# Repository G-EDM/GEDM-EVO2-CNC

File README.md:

# Schematics, Gerber files and Kicad projects for the PCBs
[>>> Schematics, Gerber files, Kicad projects and PCBway links <<<](https://github.com/G-EDM/GEDM-EVO2-CNC/tree/main/files/schematics-and-gerbers)
</br>
</br>

# GEDM-EVO2-CNC
Gantry based 3 axis CNC router with heavy duty 3d printed parts

```diff
  ______         ________ _______  __       __      ________ __     __  ______       ______ ______ 
 /      \       |        \       \|  \     /  \    |        \  \   |  \/      \     |      \      \
|  ▓▓▓▓▓▓\      | ▓▓▓▓▓▓▓▓ ▓▓▓▓▓▓▓\ ▓▓\   /  ▓▓    | ▓▓▓▓▓▓▓▓ ▓▓   | ▓▓  ▓▓▓▓▓▓\     \▓▓▓▓▓▓\▓▓▓▓▓▓
| ▓▓ __\▓▓______| ▓▓__   | ▓▓  | ▓▓ ▓▓▓\ /  ▓▓▓    | ▓▓__   | ▓▓   | ▓▓ ▓▓  | ▓▓      | ▓▓   | ▓▓  
| ▓▓|    \      \ ▓▓  \  | ▓▓  | ▓▓ ▓▓▓▓\  ▓▓▓▓    | ▓▓  \   \▓▓\ /  ▓▓ ▓▓  | ▓▓      | ▓▓   | ▓▓  
| ▓▓ \▓▓▓▓\▓▓▓▓▓▓ ▓▓▓▓▓  | ▓▓  | ▓▓ ▓▓\▓▓ ▓▓ ▓▓    | ▓▓▓▓▓    \▓▓\  ▓▓| ▓▓  | ▓▓      | ▓▓   | ▓▓  
| ▓▓__| ▓▓      | ▓▓_____| ▓▓__/ ▓▓ ▓▓ \▓▓▓| ▓▓    | ▓▓_____   \▓▓ ▓▓ | ▓▓__/ ▓▓     _| ▓▓_ _| ▓▓_ 
 \▓▓    ▓▓      | ▓▓     \ ▓▓    ▓▓ ▓▓  \▓ | ▓▓    | ▓▓     \   \▓▓▓   \▓▓    ▓▓    |   ▓▓ \   ▓▓ \
  \▓▓▓▓▓▓        \▓▓▓▓▓▓▓▓\▓▓▓▓▓▓▓ \▓▓      \▓▓     \▓▓▓▓▓▓▓▓    \▓     \▓▓▓▓▓▓      \▓▓▓▓▓▓\▓▓▓▓▓▓
```

# Downloadlinks for the freecad files
    The router file is a little crappy. The extrusions/tank/rails of the frame are not a the correct position and the Y ballscrew is too short etc.
    But it can be used

[>>> G-EDM EVOII Wire extension FreeCAD Project <<<](https://drive.google.com/file/d/1ZBrTBwRvTHIMtCySQIoWtpVMdJbfWR3E/view)
</br>
[>>> G-EDM EVOII Router FreeCAD Project <<<](https://drive.google.com/file/d/1OkYVYsVrToy4-q0G6XMzgWKsSyYXRRj4/view)
</br>
</br>

# Responsible for the content provided
    Lautensack Roland (Germany)
    Contact: goblin-dev@proton.me

# This project is still a work in progress and not fully finished yet

The GEDM-EVO2 Gantry Router uses heavy duty 3D printed parts, strong HGR20 linear rails, ballscrews and heavy profiles (40x160).

With only a few upgrades/changes it will be able to not only do EDM but also mill wood and smaller aluminum parts.

In order to do those milling jobs it may require a second ballscrew on the left side.

The wire extension used in the images is the one designed by Alex Treseder for the PicoEDM:
https://github.com/alextreseder/picoEDM

Not fully finished. Z axis is still missing and the massive aluminum plate on the front is temporary.

Check out the youtube channel:

# Legal notes

    The author of this project is in no way responsible for whatever people do with it.

    No warranty. 

# License

    All files provided are for private use only if not declared otherwise and any form of commercial use or redistribution of the protected files is prohibited. 

# Follow the project:

[>>> Follow the project on Youtube <<<](https://www.youtube.com/@G-EDM/videos)

[>>> Stay informed on Hackaday <<<](https://hackaday.io/project/190371-g-edm)

[>>> Get involved on Discord <<<](https://discord.gg/9cTsyDkEbe)

# Donations

    * Developement is not always as fast as it could be if you're poor. You want to donate something? 
    * Paypal: paypal.me/gedmdev
    * Bitcoin: bc1qkz8vwrd3pupewdtyg09qj9nv249vlgdy4ffhyv

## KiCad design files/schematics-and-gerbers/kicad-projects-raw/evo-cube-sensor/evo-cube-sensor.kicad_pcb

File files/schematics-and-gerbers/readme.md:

# Update

Added the new EVOIII PCB. This board was designed for easier manufacturing and is a replacement for the sensorboard and the pulseboard. It has both integrated on a single PCB.

The PCBs can be ordered on PCBway using following links:

# Motionboard
https://www.pcbway.com/project/shareproject/G_EDM_Low_budget_DIY_Wire_EDM_machine_34e1e043.html

# EVOIII Board (Sensorboard and Pulseboard on one PCB)
https://www.pcbway.com/project/shareproject/G_EDM_EVOIII_board_Low_budget_DIY_Wire_EDM_machine_482d5b7a.html

<br/><br/><br/><br/>
# If the EVOIII board is used the following two PCBs are not needed.
<br/><br/>

# Sensorboard (Not needed if the EVOIII board is used)
https://www.pcbway.com/project/shareproject/G_EDM_Low_budget_DIY_Wire_EDM_machine_sensorboard_24b74366.html

# Pulseboard (Not needed if the EVOIII board is used)
https://www.pcbway.com/project/shareproject/G_EDM_Low_budget_DIY_Wire_EDM_machine_pulseboard_8975f488.html

The full electronic enclosure contains the control panel with the ESP32 motion controller and a touch screen and the spark generator.

The pulseboard and the sensing unit are two dedicated PCBs stacked on top of eachother.

The sensing unit is not bound to the G-EDM pulseboard and can be used with a custom generator as well.

Currently only the schmeatics of the pulseboard PCB is uploaded here.

Sennsing unit / motionboard and gerber files will follow.

The pulseboard can be used as stand-alone board too but the sensing is not comparable to the new sense circuit that is able to capture raw watercontact and even the tiniest discharges.

Files currently provided:

Schematics:
```diff
+ Pulseboard EVO² - yes
```
```diff
+ Sensing Unit EVO² - yes
```
```diff
+ Motionboard EVO² - yes
```

Gerber files:
```diff
+ Pulseboard EVO² - yes
```
```diff
+ Sensing Unit EVO² - yes
```
```diff
+ Motionboard EVO² - yes
```

BOM:
```diff
+ Pulseboard EVO² - yes
```
```diff
+ Sensing Unit EVO² - yes
```
```diff
+ Motionboard EVO² - yes
```

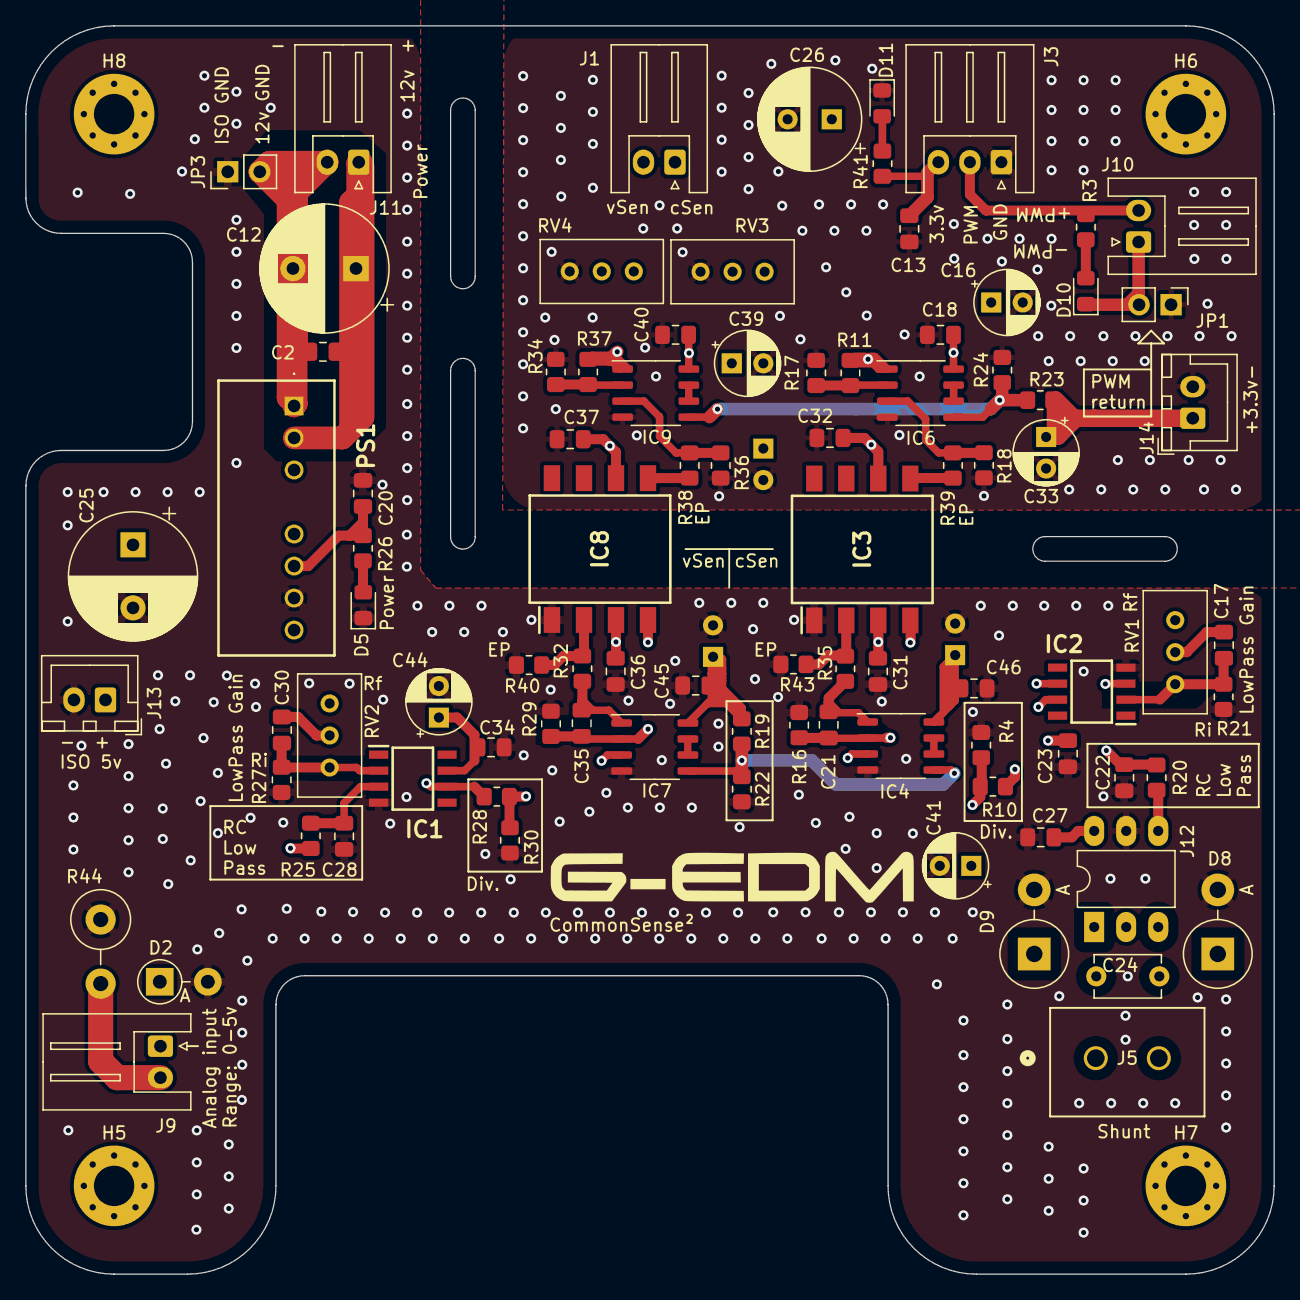
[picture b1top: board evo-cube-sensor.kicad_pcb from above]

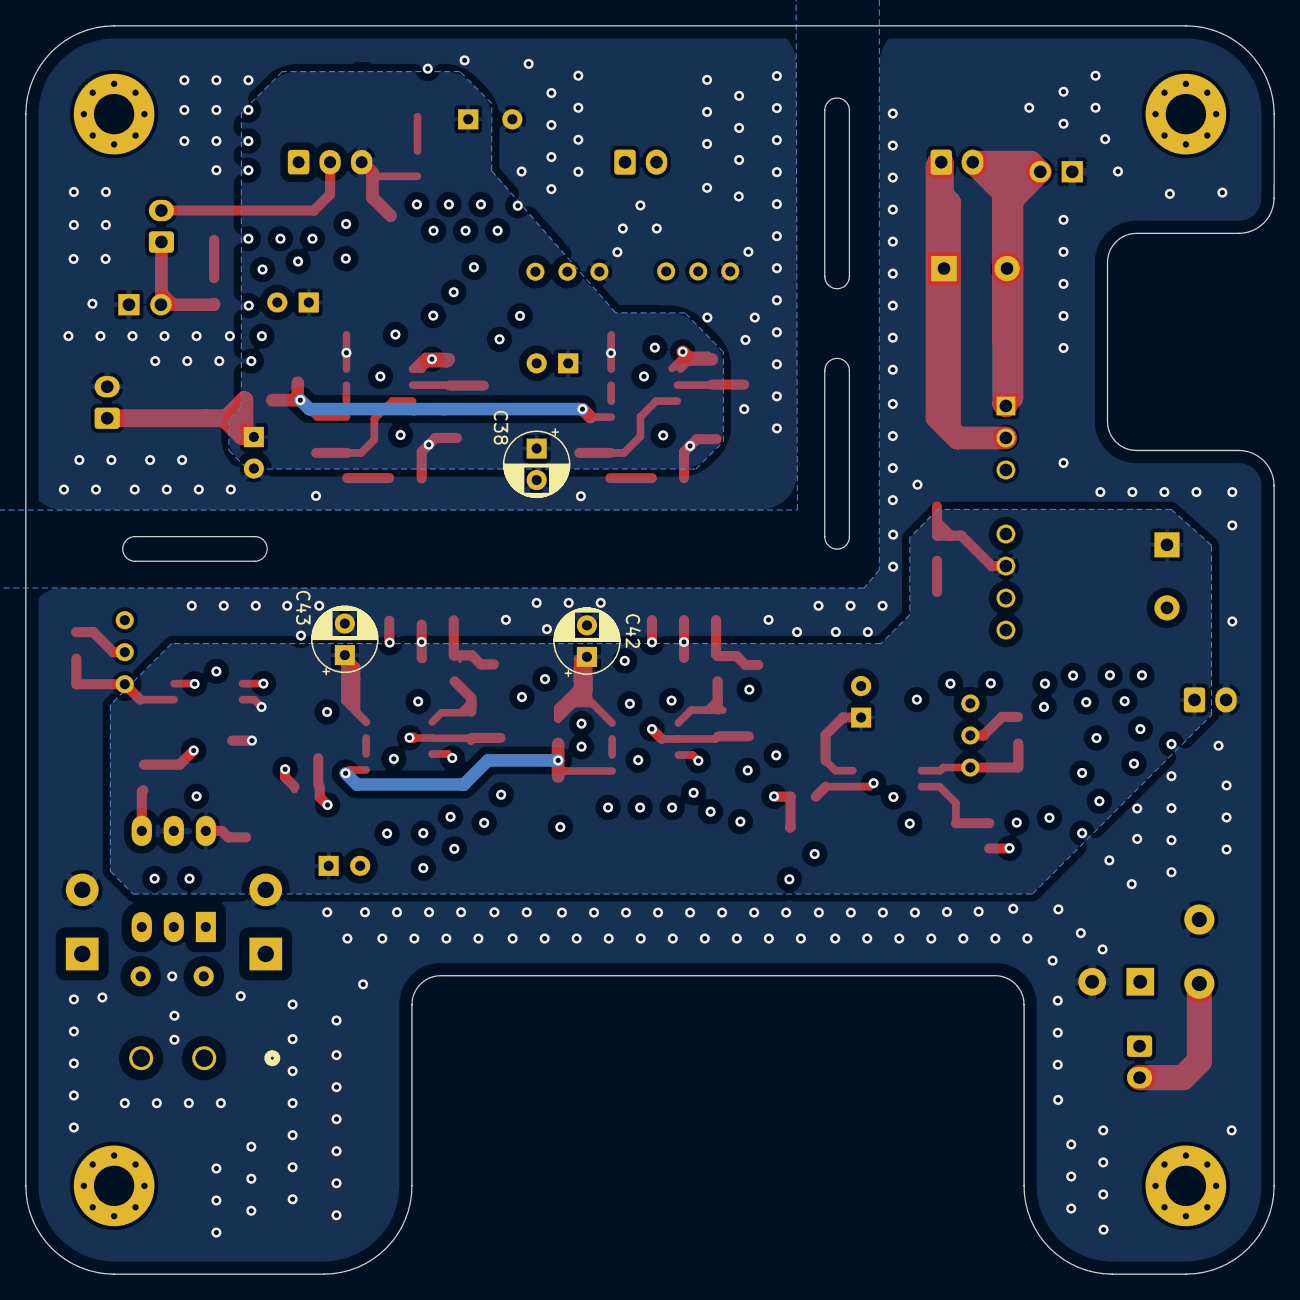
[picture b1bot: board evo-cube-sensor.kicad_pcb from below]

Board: 4 copper layers, 99.0 x 99.0 mm, 96 parts (3 on the bottom side), 46 nets.

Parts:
C2, C13, C18, C20, C23, C27, C31, C32, C34, C36, C37, C40, C45, C46: 0.1uf-50v-x7r 08055C104K4T2A; C_0805_2012Metric_Pad1.18x1.45mm_HandSolder
C12, C25: 220uf50v RD1H227M1012M128; CP_Radial_D10.0mm_P5.00mm
C16, C39, C41, C44: 47uf63v RD1J476M6L011M18; CP_Radial_D5.0mm_P2.50mm
C17, C30: 47pf X; C_0805_2012Metric_Pad1.18x1.45mm_HandSolder
C21, C22, C28, C35: 100pf50v X7R C0805C101J5RACTU; C_0805_2012Metric_Pad1.18x1.45mm_HandSolder
C24: C100pf500v KERKO-500 100P; C_Disc_D5.1mm_W3.2mm_P5.00mm
C26: 220uf35v RD1V227M0811M160; CP_Radial_D8.0mm_P3.50mm
C33, C38, C42, C43: X; CP_Radial_D5.0mm_P2.50mm
D2: 5.1v Zener (Not used); D_DO-41_SOD81_P3.81mm_Vertical_AnodeUp
D5, D11: SM0805UGC; LED_0805_2012Metric_Pad1.15x1.40mm_HandSolder
D8, D9: 1N5379B 110v Zener; D_DO-201_P5.08mm_Vertical_AnodeUp
D10: APT2012LVBC/D; LED_0805_2012Metric_Pad1.15x1.40mm_HandSolder
H5: MountingHole_Pad; MountingHole_3.2mm_M3_Pad_Via
H6, H7, H8: MountingHole; MountingHole_3.2mm_M3_Pad_Via
IC1, IC2: OPA350UA; SOIC127P600X175-8N
IC3, IC8: HCNR201-500E; SOP254P1230X400-8N
IC4, IC7: LM358F-GE2; SOP-8_3.9x4.9mm_P1.27mm
IC6, IC9: OPA2350UA; SOP-8_3.9x4.9mm_P1.27mm
J1, J9, J10, J11: JST_XH_S2B-XH-A_1x02_P2.50mm_Horizontal
J3: JST_XH_S3B-XH-A_1x03_P2.50mm_Horizontal
J5: 1776138-2 and 796641-2; CONN2_796643-2_TEC
J12: INA293B3QDBVRQ1 on PCB3007-1 Adapter; DIP-6_W7.62mm_LongPads
J13, J14: JST XHP-2; JST_XH_B2B-XH-A_1x02_P2.50mm_Vertical
JP1: Jumper_2_Bridged; PinHeader_1x02_P2.54mm_Vertical
JP3: 1x02 pin header jumper cap (149-3-002-F0-XS); PinHeader_1x02_P2.54mm_Vertical
PS1: RS3K-2405SZ/H3; RS3K2405SZH3
R3: 220; R_0805_2012Metric_Pad1.20x1.40mm_HandSolder
R4, R30: 4k7; R_0805_2012Metric_Pad1.20x1.40mm_HandSolder
R10, R19, R22, R23, R24, R28: 10k 1% WRIS-RSKS 560112120004; R_0805_2012Metric_Pad1.20x1.40mm_HandSolder
R11, R17, R34, R37: 20k RK73H2ARTTD2002F; R_0805_2012Metric_Pad1.20x1.40mm_HandSolder
R16, R18, R29, R36: 100k 1% Würth WRIS-RSKS 560112120013; R_0805_2012Metric_Pad1.20x1.40mm_HandSolder
R20, R21, R25, R27: 1kOhm 5% ERJ-T06J102V; R_0805_2012Metric_Pad1.20x1.40mm_HandSolder
R26: 560Ohm RK73B2ATTD561J; R_0805_2012Metric_Pad1.20x1.40mm_HandSolder
R32, R35: 200Ohm WRIS-RSKS 560112120015; R_0805_2012Metric_Pad1.20x1.40mm_HandSolder
R38, R39: Zero Ohm RCC08050000Z0EA; R_0805_2012Metric_Pad1.20x1.40mm_HandSolder
R40, R43: 10k?; R_0805_2012Metric_Pad1.20x1.40mm_HandSolder
R41: 220 Ohm 5% ERJ-T06J221V; R_0805_2012Metric_Pad1.20x1.40mm_HandSolder
R44: 1kOhm; R_Axial_DIN0414_L11.9mm_D4.5mm_P5.08mm_Vertical
RV1, RV2, RV3, RV4: 3296W Poti 10kOhm; Potentiometer_Bourns_3296W_Vertical

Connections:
1,65V: IC6.5 (2IN+), IC9.5 (2IN+), R23.2, R24.1
2.5V: IC4.5 (2IN+), IC7.5 (2IN+), R19.2, R22.1
+12v-from-pb: C2.1, C12.1, J11.1, PS1.2 (+VIN)
ESP3.3v: C13.1, C16.1, C18.1, C26.1, C32.1, C33.1, C37.1, C38.1, C39.1, C40.1, IC3.6 (PD2_CATHODE), IC6.8 (VCC), IC8.6 (PD2_CATHODE), IC9.8 (VCC), J3.3, J14.1, R23.1, R41.2
GND1: C13.2, C16.2, C18.2, C26.2, C32.2, C33.2, C37.2, C38.2, C39.2, C40.2, D11.1 (K), IC6.4 (GND), IC9.4 (GND), J3.1, J14.2, JP1.1 (A), R17.1, R18.1, R24.2, R34.1, R36.1, RV3.3, RV4.3
GND3: C20.2, C22.2, C23.2, C25.2, C27.1, C28.2, C31.1, C34.2, C36.1, C41.2, C42.2, C43.2, C44.2, C45.1, C46.1, D2.2 (A), D5.1 (K), D8.2 (A), D9.2 (A), IC1.4 (V-), IC2.4 (V-), IC3.1 (LED_CATHODE), IC4.4 (GND), IC7.4 (GND), IC8.1 (LED_CATHODE), J12.5, J13.2, JP3.1 (A), PS1.7 (-VOUT), R4.2, R16.1, R21.2, R22.2, R27.2, R29.1, R30.2, R40.2, R43.2, R44.1
ISO+5v: C20.1, C23.1, C25.1, C27.2, C31.2, C34.1, C36.2, C41.1, C42.1, C43.1, C44.1, C45.2, C46.2, IC1.7 (V+), IC2.7 (V+), IC3.3 (PD1_CATHODE), IC4.8 (VCC), IC7.8 (VCC), IC8.3 (PD1_CATHODE), J12.6, J13.1, PS1.6 (+VOUT), R19.1, R26.2
Isolated-csense-out: J1.1, RV3.2
Isolated-vsense-out: J1.2, RV4.2
unnamed: D2.1 (K), J9.1, R25.1
unnamed: D5.2 (A), R26.1
unnamed: C24.1, D8.1 (K), J5.2, J12.3
unnamed: C24.2, D9.1 (K), J5.1, J12.1
unnamed: D10.2 (A), R3.1
unnamed: D10.1 (K), J10.1, JP1.2 (B)
unnamed: D11.2 (A), R41.1
unnamed: C28.1, IC1.3 (+IN), R25.2
unnamed: C30.2, IC1.2 (-IN), R27.1, RV2.1
unnamed: C30.1, IC1.6 (OUTPUT), R28.2, RV2.2
unnamed: C22.1, IC2.3 (+IN), R20.2
unnamed: C17.2, IC2.2 (-IN), R21.1, RV1.1
unnamed: C17.1, IC2.6 (OUTPUT), R10.2, RV1.2
unnamed: IC3.2 (LED_ANODE), R35.1, R43.1
unnamed: C21.1, IC3.4 (PD1_ANODE), IC4.2 (1IN-), R16.2
unnamed: IC3.5 (PD2_ANODE), R39.1
unnamed: IC4.3 (1IN+), R4.1, R10.1
unnamed: C21.2, IC4.1 (1OUT), R35.2
unnamed: IC4.6 (2IN-), IC4.7 (2OUT)
unnamed: IC6.3 (1IN+), R18.2, R39.2
unnamed: IC6.2 (1IN-), R11.1, R17.2
unnamed: IC6.1 (1OUT), R11.2, RV3.1
unnamed: IC6.6 (2IN-), IC6.7 (2OUT)
unnamed: IC7.3 (1IN+), R28.1, R30.1
unnamed: C35.1, IC7.2 (1IN-), IC8.4 (PD1_ANODE), R29.2
unnamed: C35.2, IC7.1 (1OUT), R32.2
unnamed: IC7.6 (2IN-), IC7.7 (2OUT)
unnamed: IC8.2 (LED_ANODE), R32.1, R40.1
unnamed: IC8.5 (PD2_ANODE), R38.1
unnamed: IC9.3 (1IN+), R36.2, R38.2
unnamed: IC9.2 (1IN-), R34.2, R37.1
unnamed: IC9.1 (1OUT), R37.2, RV4.1
unnamed: IC9.6 (2IN-), IC9.7 (2OUT)
unnamed: J9.2, R44.2
unnamed: J12.4, R20.1
pwm-from-esp: J3.2, J10.2, R3.2
to-gnd2-on-pb: C2.2, C12.2, J11.2, JP3.2 (B), PS1.1 (-VIN)

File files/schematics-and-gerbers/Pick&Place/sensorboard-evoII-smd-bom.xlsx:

| G-EDM Sensorboard EVOII – SMD/SMT BOM
Item # | *Designator | *Qty | Manufacturer | *Mfg Part # | Description / Value | *Package/Footprint | Type | Your Instructions / Notes
1 | C2,C13,C18,C20,C23,C27,C31,C32,C34,C36,C37,C40,C45,C46 | 14 | KYOCERA AVX | 08055C104K4T2A | 0.1uf 50v X7R 10% MLCC | 0805 | SMD
2 | C21,C22,C28,C35 | 4 | KEMET | C0805C101J5RACTU | 100pF 50v X7R 5% MLCC | 0805 | SMD
3 | R38,R39 | 2 | Vishay / Dale | RCC08050000Z0EA | Zero Ohm 1/4W resistor jumper | 0805 | SMD
4 | R32,R35 | 2 | Würth | 560112120015 | 200 Ohm 1/4W 1% resistor | 0805 | SMD
5 | R3,R41 | 2 | Panasonic | ERJ-T06J221V | 220 Ohm 1/4W 5% resistor | 0805 | SMD
6 | R26 | 1 | KOA Speer | RK73B2ATTD561J | 560 Ohm 1/4W 5% resistor | 0805 | SMD
7 | R20,R21,R25,R27 | 4 | Panasonic | ERJ-T06J102V | 1 kOhm 1/4W 5% resistor | 0805 | SMD
8 | R4,R30 | 2 | Vishay / Dale | RCC08054K70FKEA | 4.7 kOhm 1/4W 1% resistor | 0805 | SMD
9 | R10,R19,R22,R23,R24,R28 | 6 | Würth | 560112120004 | 10 kOhm 1/4W 1% resistor | 0805 | SMD
10 | R11,R17,R34,R37 | 4 | KOA Speer | RK73H2ARTTD2002F | 20 kOhm 1/4W 1% resistor | 0805 | SMD
11 | R16,R18,R29,R36 | 4 | Würth | 560112120013 | 100 kOhm 1/4W 1% resistor | 0805 | SMD
12 | IC1,IC2 | 2 | Texas Instruments | OPA350UA | High Speed rail-to-rail OpAmp single channel | SOIC-8 | SMD | Please validate the footprint
13 | IC6,IC9 | 2 | Texas Instruments | OPA2350UA | High Speed rail-to-rail OpAmp dual channel | SOIC-8 | SMD | Please validate the footprint
14 | IC8,IC3 | 2 | Broadcom / Avago | HCNR201-500E | High Linear Optocoupler | SOP-8 | SMD | Please validate the footprint
15 | IC4,IC7 | 2 | ROHM Semiconductor | LM358F-GE2 | Dual Grnd Sense Op Amp | SOP-8 | SMD | Please validate the footprint
16 | D5,D11 | 2 | Bivar | SM0805UGC | LED green 20mA 2v | 0805 | SMD
17 | D10 | 1 | Kingbright | APT2012LVBC/D | LED blue low current (starts to emit at 2mA) 2,65v | 0805 | SMD

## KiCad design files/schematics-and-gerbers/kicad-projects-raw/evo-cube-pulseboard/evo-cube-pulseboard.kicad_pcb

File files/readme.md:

The sensorboard and the pulseboard are connected with 3 JST connectors.

The connectors are placed at the exact same position. Don't use the wrong connector!
I shared a few images in the past where the PWM from the sensorboard was connected to the 5v output on the
pulseboard. It will burn the ESP32.

Sensorboard => Pulseboard

J10 => J8
J11 => J2
J9  => J7

Before connecting J9 to J7 make sure the voltage on J7 is below 5v! This is important. Use the Poti on the pulseboard to adjust it while
the PSU is ON. The output of J7 should remain a little below 5v at the max voltage provided from the DPM.

If a higher voltage is used adjust the Poti again. 
If 80v is used the output should be 4.8v while the big terminal is at 80v.
If 60v is used the output should be 4.8v while the big terminal is at 60v.

The board has 100v Zener diodes. Up to 90v should be ok.

The sensorboard provides 3.3v output and isolated 5v output. It is not used for anything yet.
The pulseboard provides 5v output that is also not used.

The pulseboard also provides a 12v output to connect a fan but it is not tested. Cheap high speed fans may introduce noise. There are flyback diodes
but if used connect a larger slow fan like a 120mm arctic fan.

# DPM to pulseboard

Connect the DPM8605 negative to the left side of the left big terminal (J19) and the positive to the right side of the same terminal.

The left side of the right terminal (J17) is bridged to the left terminals positive. The Shunt and wire is always hot and only GND is switched.
Connect the left side of J17 to one side of the shunt and the other side is the spark positive output.
The spark negative goes back into the right side of J17.

# Shunt to sensorboard
Connect both sides of the shunt to the sensorboard J5. It is no problem to wire it wrong here. If connected wrong it will not provide a feedback but will not destroy anything. Just swap the wire if there is no feedback.

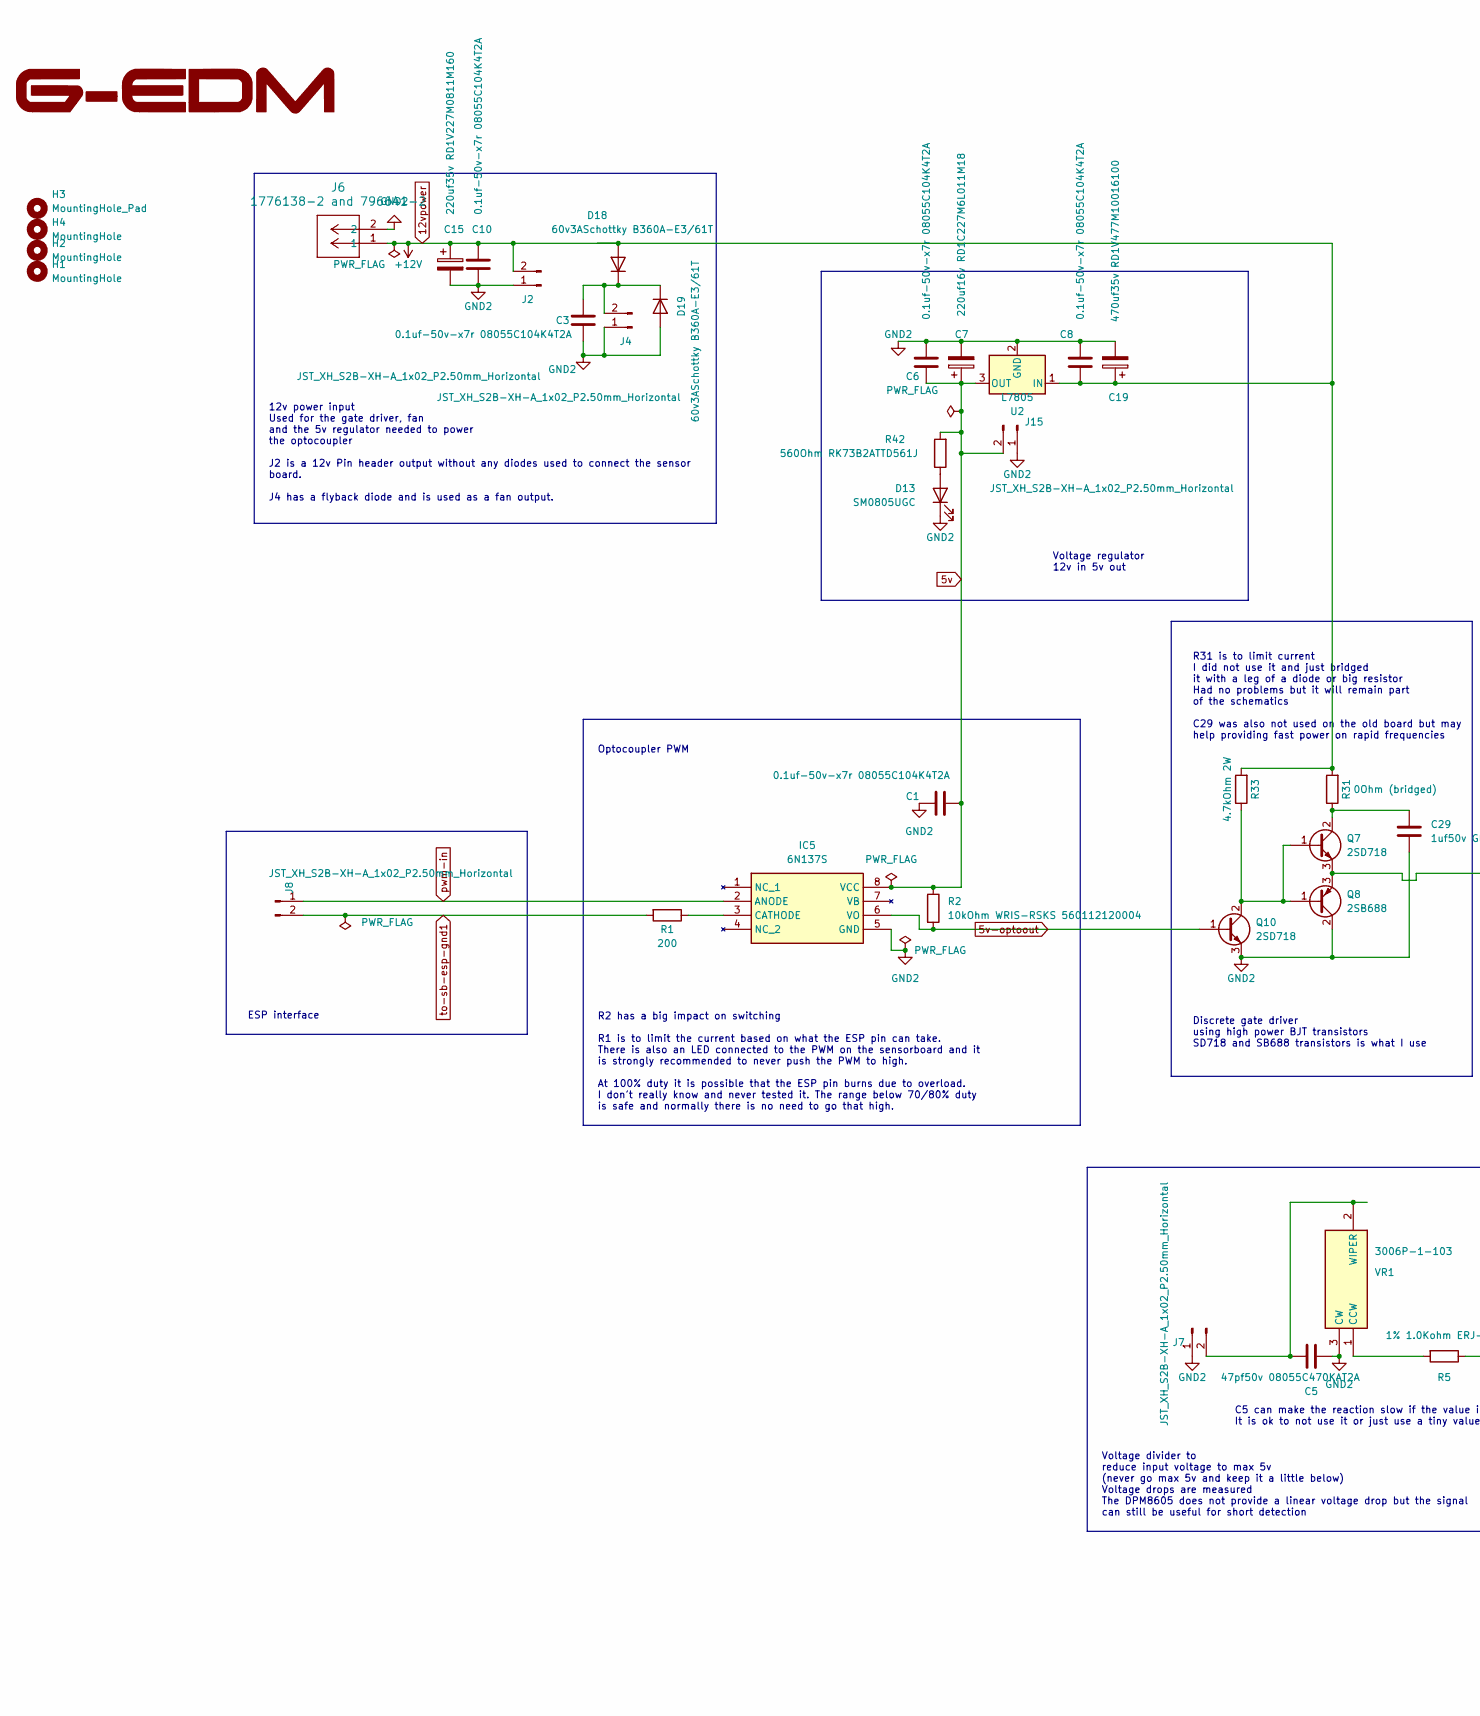
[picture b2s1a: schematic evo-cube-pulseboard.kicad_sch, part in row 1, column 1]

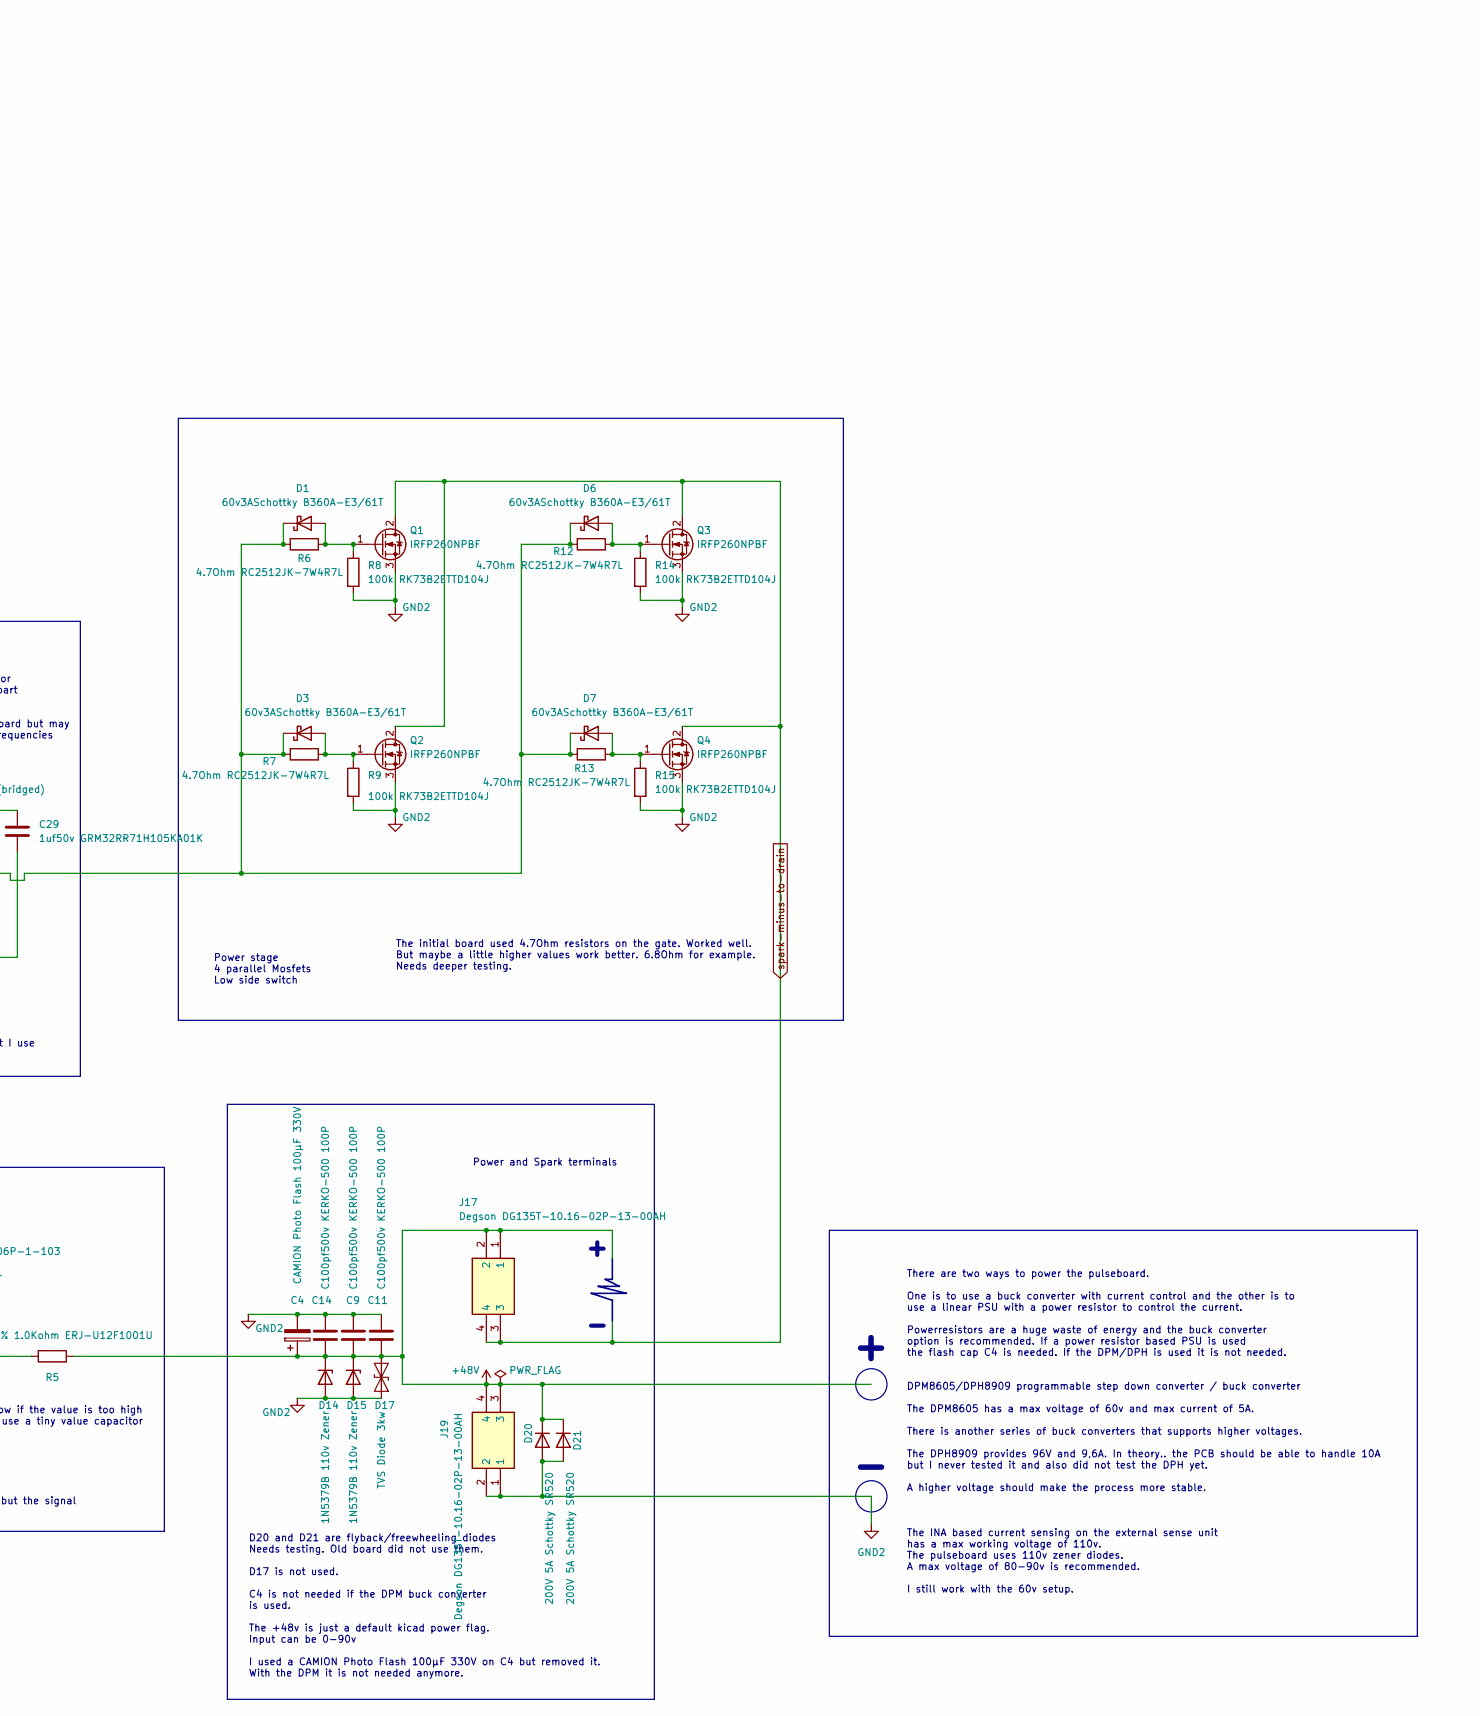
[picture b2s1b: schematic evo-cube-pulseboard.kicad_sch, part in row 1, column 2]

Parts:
C1, C3, C6, C8, C10: 0.1uf-50v-x7r 08055C104K4T2A; C_0805_2012Metric_Pad1.18x1.45mm_HandSolder
C4: CAMION Photo Flash 100µF 330V; CP_Radial_D14.0mm_P5.00mm
C5: 47pf50v 08055C470KAT2A; C_1206_3216Metric_Pad1.33x1.80mm_HandSolder
C7: 220uf16v RD1C227M6L011M18; CP_Radial_D6.3mm_P2.50mm
C9, C11, C14: C100pf500v KERKO-500 100P; C_Disc_D5.0mm_W2.5mm_P5.00mm
C15: 220uf35v RD1V227M0811M160; CP_Radial_D8.0mm_P3.50mm
C19: 470uf35v RD1V477M10016100; CP_Radial_D10.0mm_P5.00mm
C29: 1uf50v GRM32RR71H105KA01K; C_1210_3225Metric_Pad1.33x2.70mm_HandSolder
D1, D3, D6, D7, D18, D19: 60v3ASchottky B360A-E3/61T; D_SMA_Handsoldering
D13: SM0805UGC; LED_0805_2012Metric_Pad1.15x1.40mm_HandSolder
D14, D15: 1N5379B 110v Zener; D_DO-201_P5.08mm_Vertical_AnodeUp
D17: TVS Diode 3kw; D_SMC_Handsoldering
D20, D21: 200V 5A Schottky SR520; D_DO-201_P5.08mm_Vertical_AnodeUp
H1, H2, H4: MountingHole; MountingHole_3.2mm_M3_Pad_Via
H3: MountingHole_Pad; MountingHole_3.2mm_M3_Pad_Via
IC5: 6N137S; SOP254P1016X460-8N; Manufacturer_Part_Number 6N136S; Mouser Part Number 859-6N136S
J2, J4, J7, J8, J15: JST_XH_S2B-XH-A_1x02_P2.50mm_Horizontal
J6: 1776138-2 and 796641-2; CONN2_796643-2_TEC
J17, J19: Degson DG135T-10.16-02P-13-00AH; DEGSONDG135T101602P1300AH; Manufacturer_Part_Number DEGSON DG135T-10.16-02P-13-00AH
Q1, Q2, Q3, Q4: IRFP260NPBF; TO-247-3_Horizontal_TabUp
Q7, Q10: 2SD718; TO-3PB-3_Vertical
Q8: 2SB688; TO-3PB-3_Vertical
R1: 200; R_0805_2012Metric_Pad1.20x1.40mm_HandSolder
R2: 10kOhm WRIS-RSKS 560112120004; R_0805_2012Metric_Pad1.20x1.40mm_HandSolder
R5: 1% 1.0Kohm ERJ-U12F1001U; R_1812_4532Metric_Pad1.30x3.40mm_HandSolder
R6, R7, R12, R13: 4.7Ohm RC2512JK-7W4R7L; R_2512_6332Metric_Pad1.40x3.35mm_HandSolder
R8, R9, R14, R15: 100k RK73B2ETTD104J; R_1210_3225Metric
R31: 0Ohm (bridged); R_Axial_DIN0414_L11.9mm_D4.5mm_P5.08mm_Vertical
R33: 4.7kOhm 2W; R_Axial_DIN0411_L9.9mm_D3.6mm_P5.08mm_Vertical
R42: 560Ohm RK73B2ATTD561J; R_0805_2012Metric_Pad1.20x1.40mm_HandSolder
U2: L7805; TO255P460X1020X2008-3P
VR1: 3006P-1-103; 3006P1103; Manufacturer_Part_Number 3006P-1-103; Mouser Part Number 652-3006P-1-103

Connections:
5v: C1.1, C6.1, C7.1, IC5.8 (VCC), J15.2, R2.1, R42.2, U2.3 (OUT)
5v-optoout: IC5.6 (VO), Q10.1 (B), R2.2
12vpower: C8.1, C10.1, C15.1, C19.1, D18.2 (A), J2.2, J6.1, R31.2, R33.2, U2.1 (IN)
+48V: C4.1, C9.1, C11.1, C14.1, D14.1 (K), D15.1 (K), D17.1 (A1), D20.1 (K), D21.1 (K), J17.1, J17.2, J19.3, J19.4, R5.1
GND2: C1.2, C3.1, C4.2, C5.2, C6.2, C7.2, C8.2, C9.2, C10.2, C11.2, C14.2, C15.2, C19.2, C29.2, D13.1 (K), D14.2 (A), D15.2 (A), D17.2 (A2), D19.2 (A), D20.2 (A), D21.2 (A), IC5.5 (GND), J2.1, J4.1, J6.2, J7.1, J15.1, J19.1, J19.2, Q1.3 (S), Q2.3 (S), Q3.3 (S), Q4.3 (S), Q8.2 (C), Q10.3 (E), R8.2, R9.2, R14.2, R15.2, U2.2 (GND), VR1.3 (CW)
unnamed: D1.2 (A), Q1.1 (G), R6.1, R8.1
unnamed: D1.1 (K), D3.1 (K), D6.1 (K), D7.1 (K), Q7.3 (E), Q8.3 (E), R6.2, R7.2, R12.2, R13.2
unnamed: D3.2 (A), Q2.1 (G), R7.1, R9.1
unnamed: D6.2 (A), Q3.1 (G), R12.1, R14.1
unnamed: D7.2 (A), Q4.1 (G), R13.1, R15.1
unnamed: D13.2 (A), R42.1
unnamed: C3.2, D18.1 (K), D19.1 (K), J4.2
unnamed: IC5.3 (CATHODE), R1.1
unnamed: C5.1, J7.2, VR1.2 (WIPER)
unnamed: C29.1, Q7.2 (C), R31.1
unnamed: Q7.1 (B), Q8.1 (B), Q10.2 (C), R33.1
unnamed: R5.2, VR1.1 (CCW)
pwm-in: IC5.2 (ANODE), J8.1
spark-minus-to-drain: J17.3, J17.4, Q1.2 (D), Q2.2 (D), Q3.2 (D), Q4.2 (D)
to-sb-esp-gnd1: J8.2, R1.2

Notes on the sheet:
There are two ways to power the pulseboard. One is to use a buck converter with current control and the other is to use a linear PSU with a power resistor to control the current. Powerresistors are a huge waste of energy and the buck converter option is recommended. If a power resistor based PSU is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
C5 can make the reaction slow if the value is too high It is ok to not use it or just use a tiny value capacitor
Power stage 4 parallel Mosfets Low side switch
R31 is to limit current I did not use it and just bridged it with a leg of a diode or big resistor Had no problems but it will remain part of the schematics C29 was also not used on the old board but may help providing fast power on rapid frequencies
Optocoupler PWM
Voltage divider to reduce input voltage to max 5v (never go max 5v and keep it a little below) Voltage drops are measured The DPM8605 does not provide a linear voltage drop but the signal can still be useful for short detection
Power and Spark terminals
R2 has a big impact on switching R1 is to limit the current based on what the ESP pin can take. There is also an LED connected to the PWM on the sensorboard and it is strongly recommended to never push the PWM to high. At 100% duty it is possible that the ESP pin burns due to overload. I don't real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
12v power input Used for the gate driver, fan and the 5v regulator needed to power the optocoupler J2 is a 12v Pin header output without any diodes used to connect the sensor board. J4 has a flyback diode and is used as a fan output.
Discrete gate driver using high power BJT transistors SD718 and SB688 transistors is what I use
D20 and D21 are flyback/freewheeling diodes Needs testing. Old board did not use them. D17 is not used. C4 is not needed if the DPM buck converter is used. The +48v is just a default kicad power flag. Input can be 0-90v I used a CAMION Photo Flash 100µF 330V on C4 but removed it. With the DPM it is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
Voltage regulator 12v in 5v out
The initial board used 4.7Ohm resistors on the gate. Worked well. But maybe a little higher values work better. 6.8Ohm for example. Needs deeper testing.
ESP interface

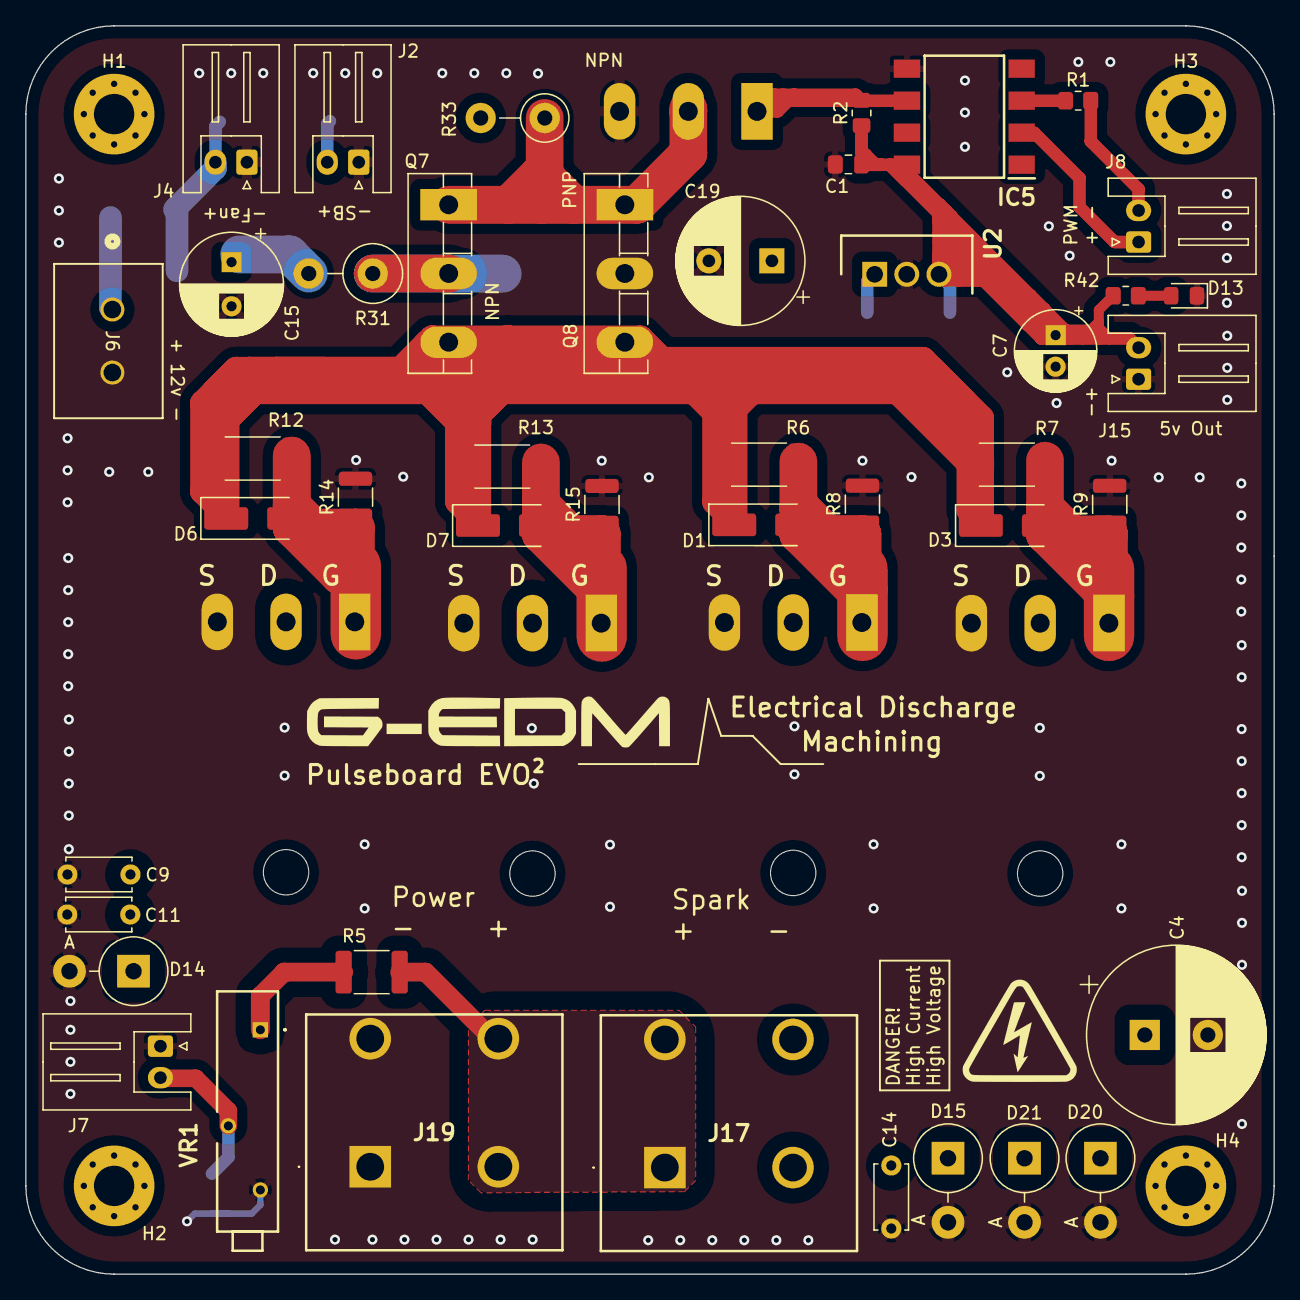
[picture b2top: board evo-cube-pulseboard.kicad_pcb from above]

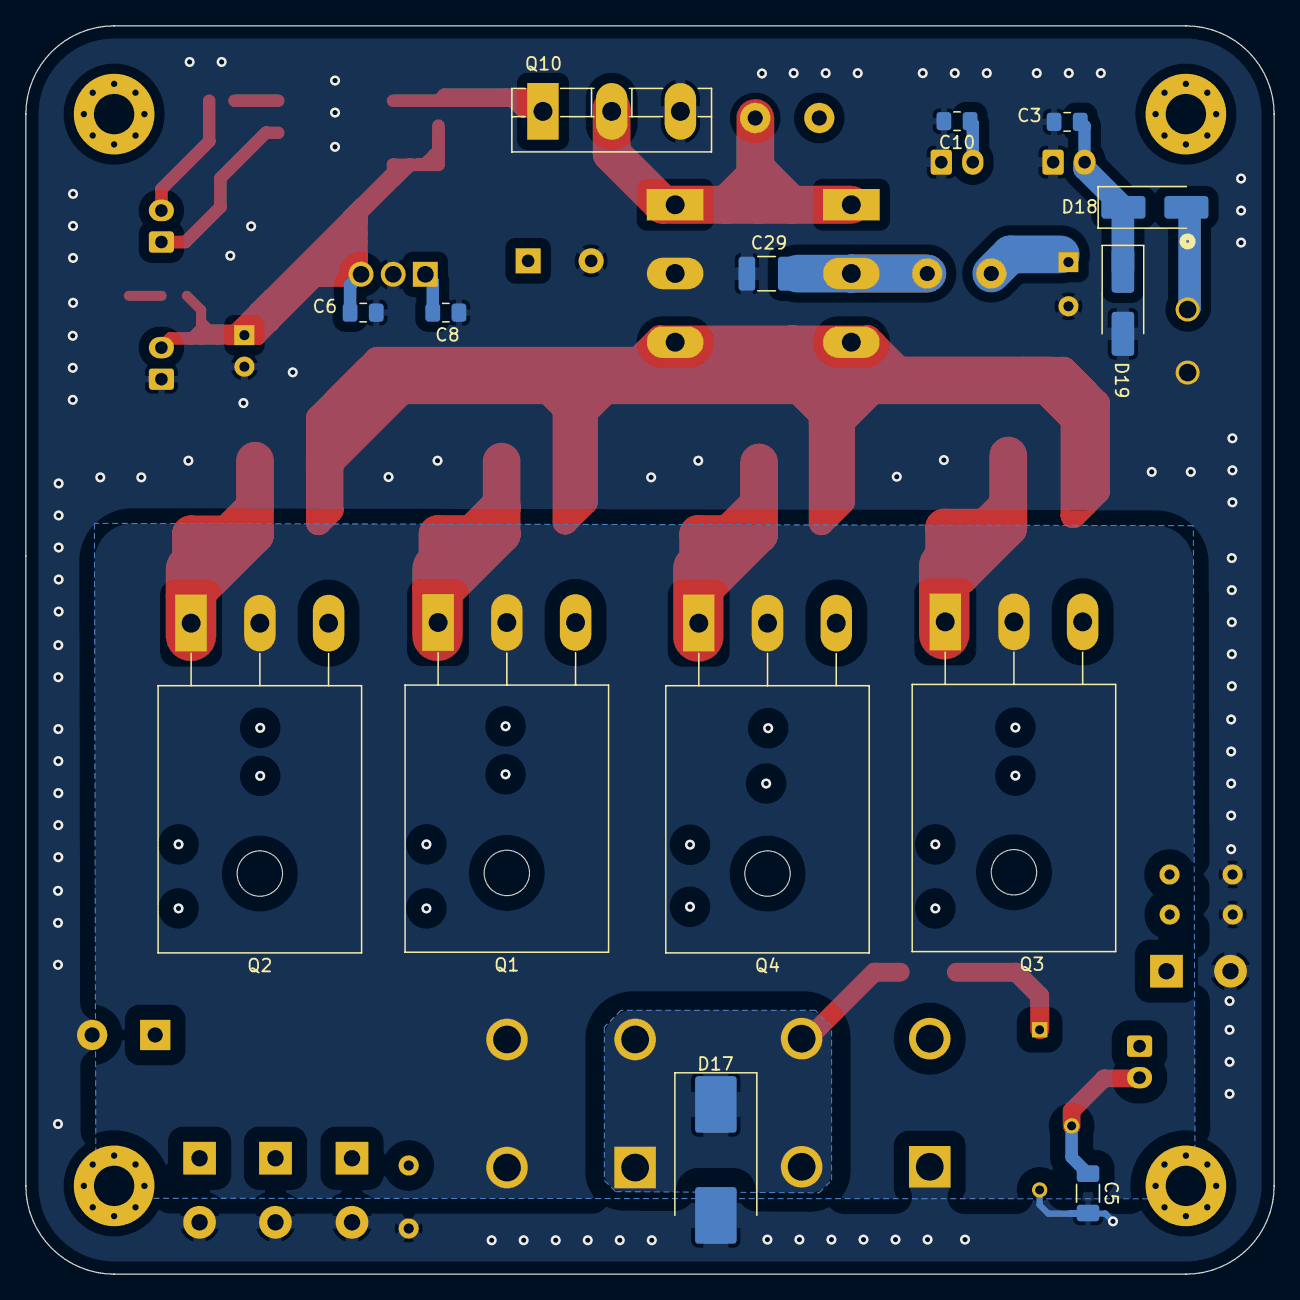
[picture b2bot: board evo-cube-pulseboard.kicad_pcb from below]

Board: 4 copper layers, 99.0 x 99.0 mm, 62 parts (14 on the bottom side), 20 nets.
